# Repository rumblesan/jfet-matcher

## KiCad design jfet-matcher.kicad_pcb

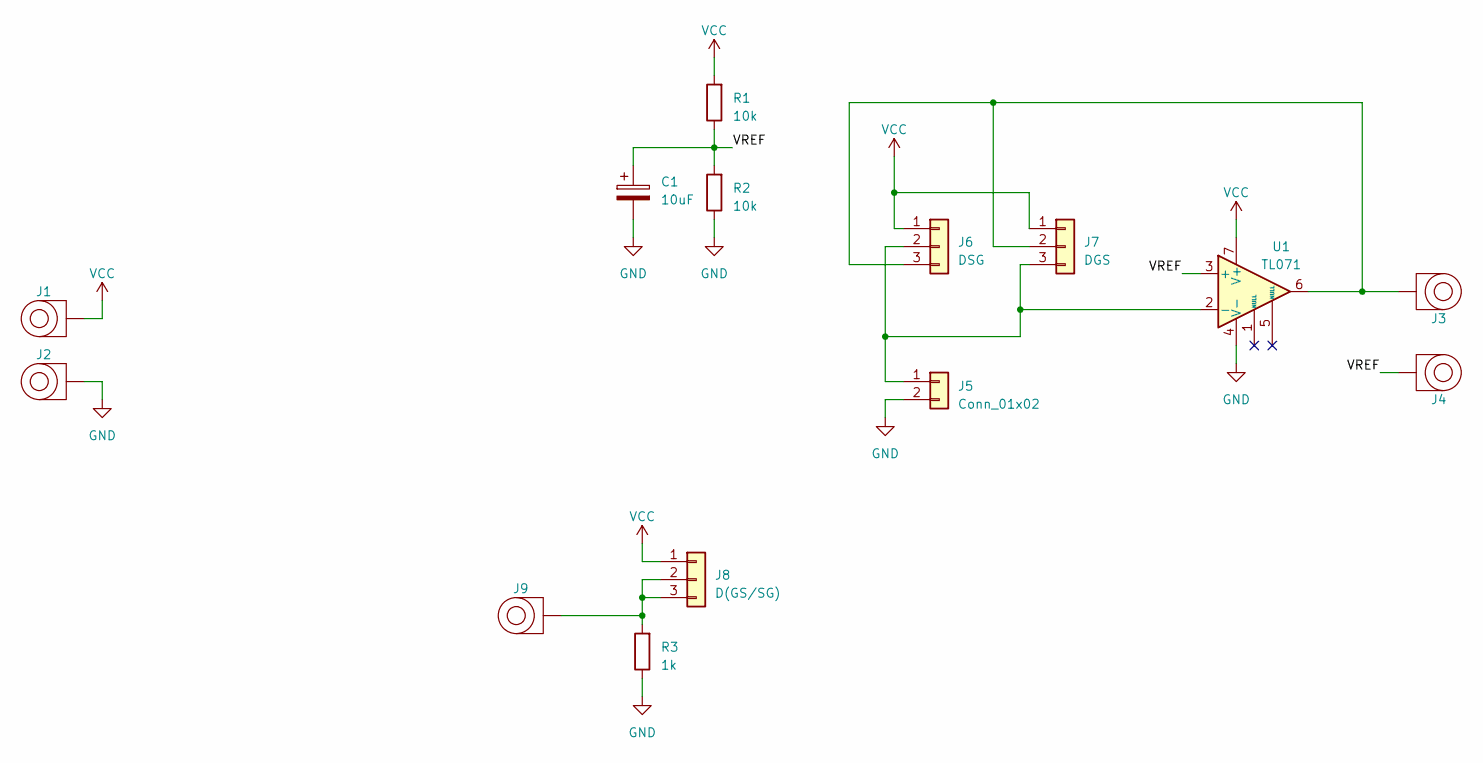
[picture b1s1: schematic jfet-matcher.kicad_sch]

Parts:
C1: 10uF; CP_Radial_D5.0mm_P2.00mm; Tolerance 20%; Voltage 50v
J1, J2, J3, J4, J9: Banana Socket PCBMount; Deltron_571_PCB_BananaJack
J5: Conn_01x02; PinSocket_1x02_P2.54mm_Vertical
J6: DSG; PinSocket_1x03_P2.54mm_Vertical
J7: DGS; PinSocket_1x03_P2.54mm_Vertical
J8: D(GS/SG); PinSocket_1x03_P2.54mm_Vertical
R1, R2: 10k; R_Axial_DIN0207_L6.3mm_D2.5mm_P10.16mm_Horizontal; Tolerance 1%
R3: 1k; R_Axial_DIN0207_L6.3mm_D2.5mm_P10.16mm_Horizontal; Tolerance 1%
U1: TL071; DIP-8_W7.62mm_Socket

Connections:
/VREF: C1.1, J4.1, R1.1, R2.2, U1.3 (+)
GND: C1.2, J2.1, J5.2, R2.1, R3.1, U1.4 (V-)
unnamed: J5.1, J6.2, J7.3, U1.2 (-)
unnamed: J3.1, J6.3, J7.2, U1.6
unnamed: J8.2, J8.3, J9.1, R3.2
VCC: J1.1, J6.1, J7.1, J8.1, R1.2, U1.7 (V+)

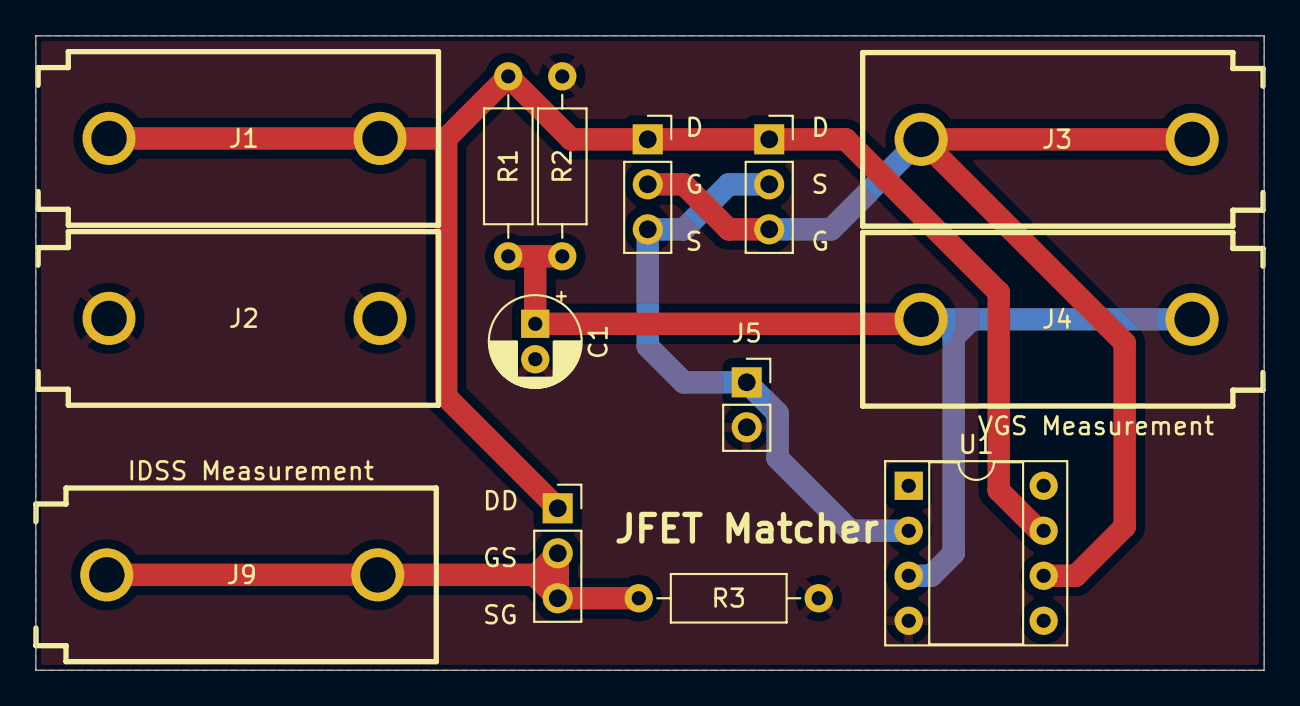
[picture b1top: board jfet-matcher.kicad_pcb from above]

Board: 2 copper layers, 69.3 x 35.8 mm, 14 parts (0 on the bottom side), 6 nets.

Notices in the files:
jfet-matcher.kicad_pcb:
creativecommons.org/licenses/by/4.0
License: CC BY 4.0
